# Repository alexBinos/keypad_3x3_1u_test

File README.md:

# keypad_3x3_1u_test

Sharing progress on the 3x3 macro keypad...

## Assembly notes

1. RGB LEDs
   - Pin 1 is marked on the PCB in silkscreen, note that the odd pin on the LED package is GND (pin 3).
   - The LEDs are designed to be placed on the back side of the PCB, facing towards the front, through the cut out.
   - To assist PCB routing, **not all LEDs are oriented in the same direction**, pay close attention to the pin 1 markings on each LED footprint.
   - The cutouts for the bottom most LEDs (D13, D16, D19) was deliberately made 0.4mm wider than the others to test the PCB footprint. This footprint wont be used on future designs.

<br/>

2. Component orientations
   - The pin 1 marker on the KC2016K 16MHz crystal oscillator (X1) and the SRV05-4 TVS diode array (U3) were not placed.
   - With the USB connector facing up:
      - Pin 1 of X1 is the **top right** pad.
      - Pin 1 of U3 is the **top left** pad.

<br/>

3. Entering the bootloader
   - Through the ISP interface, disable the HWBE fuse and enable the BOOTRST fuse.
   - Flash the Caterina bootloader
   - See section 27 of the ATMEGA32U4 datasheet for more details.

<br/>

4. Non-critical hardware bugs
   - The series termination resistor for the RGB LEDs was not placed, the LEDS still work but this may affect their reliability.
   - Pads for the reset switch are slightly too small for the switch provided but you can still make it fit

<br/>

5. If you find any more issues or have feedback for the next revision let me know

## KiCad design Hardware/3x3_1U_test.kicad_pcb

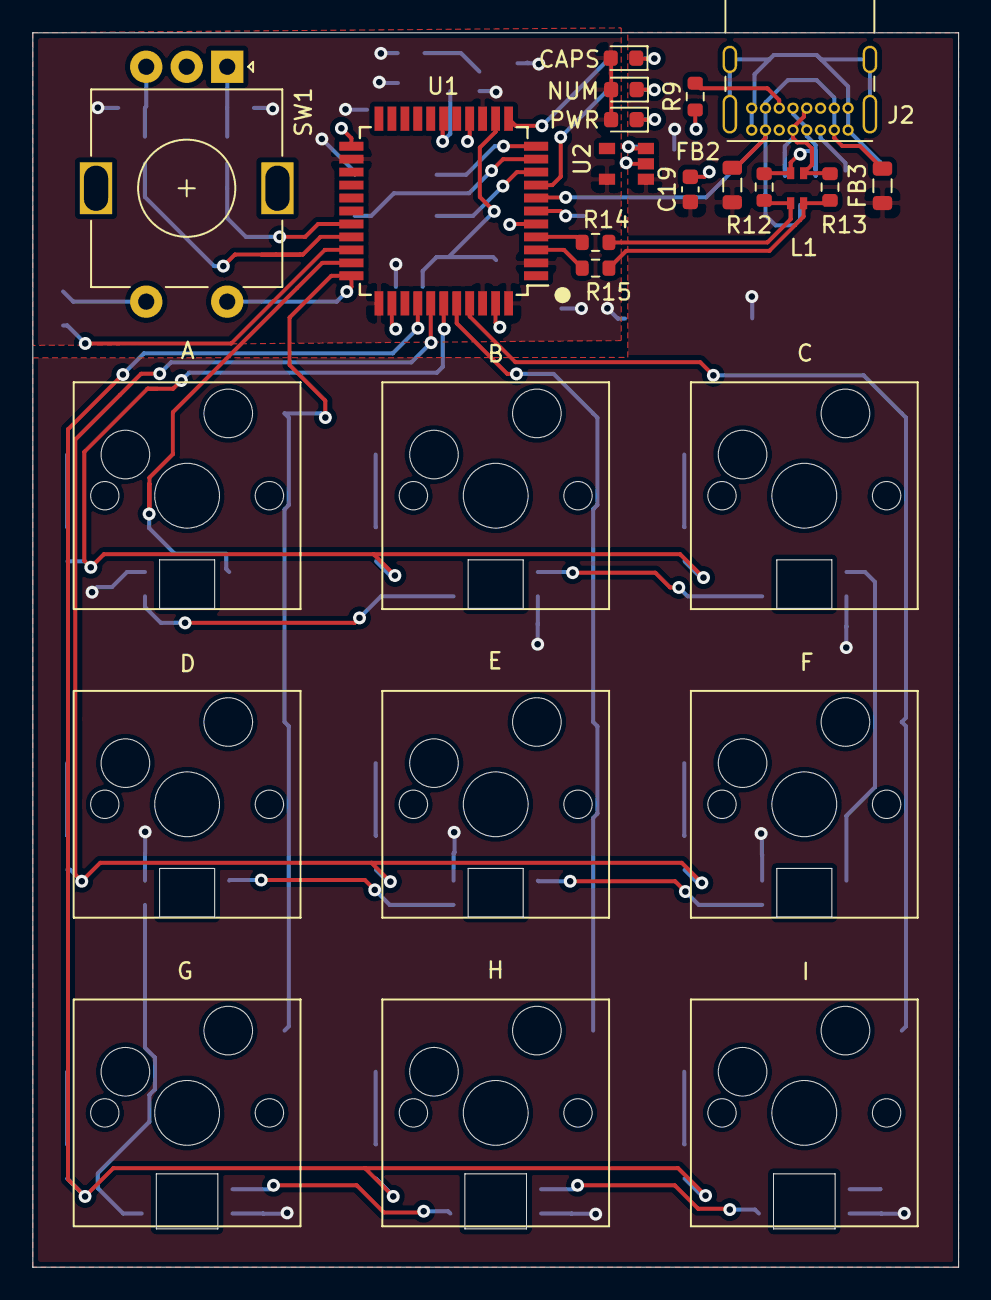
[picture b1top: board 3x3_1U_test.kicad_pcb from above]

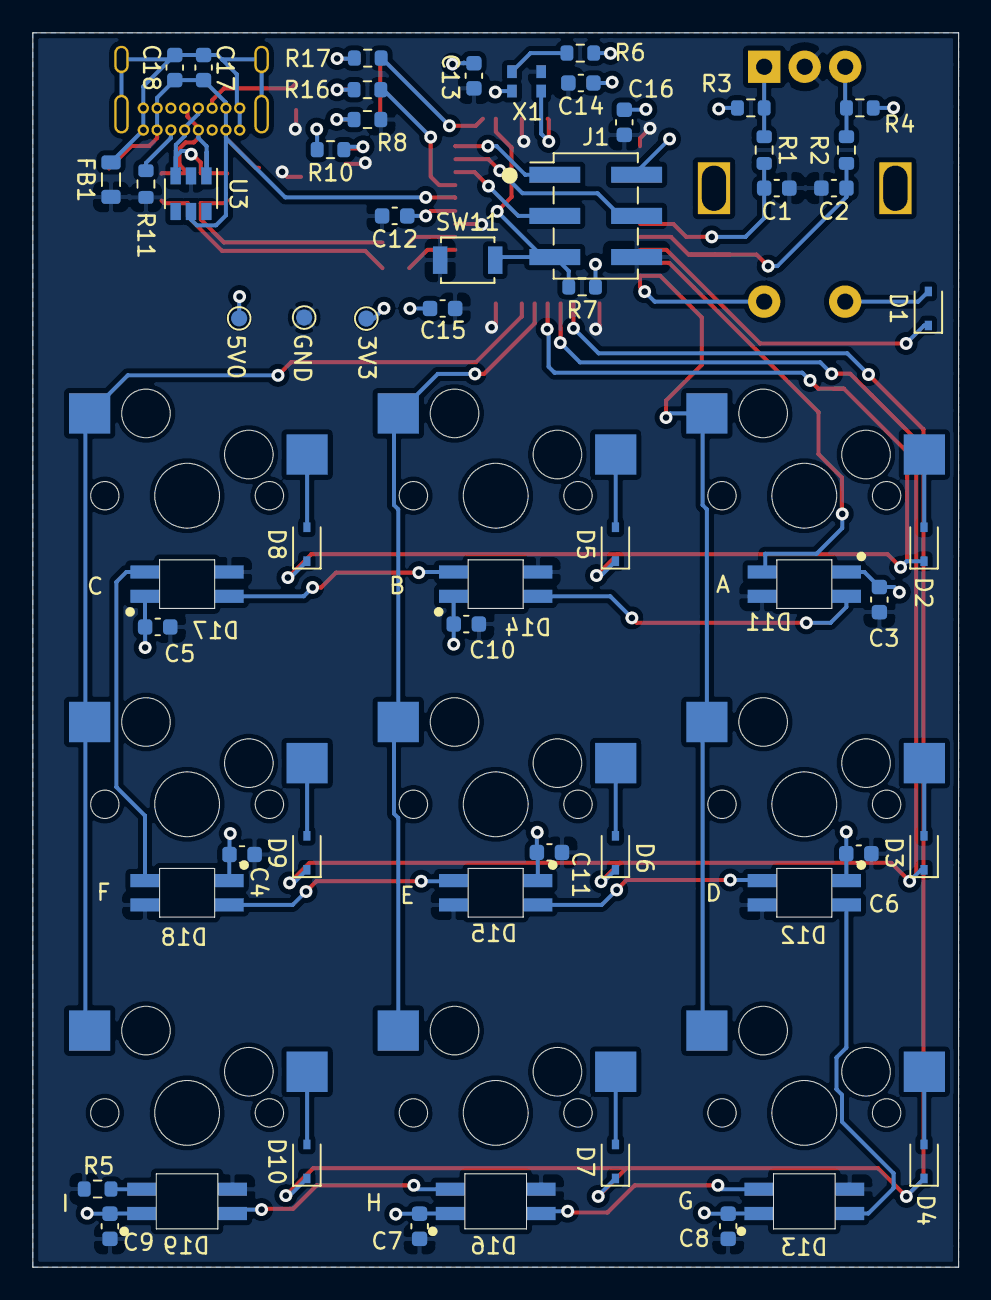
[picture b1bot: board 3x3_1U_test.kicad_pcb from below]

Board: 2 copper layers, 57.2 x 76.2 mm, 82 parts (48 on the bottom side), 57 nets.

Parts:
C1, C2, C3, C4, C5, C6, C7, C8, C9, C10, C11, C13, C14, C15, C19: 100nF; C_0603_1608Metric
C12, C16, C18: 1uF; C_0603_1608Metric
C17: 10uF; C_0603_1608Metric
D1: SWITCH; D_SOD-323
D2: A; D_SOD-323
D3: D; D_SOD-323
D4: G; D_SOD-323
D5: B; D_SOD-323
D6: E; D_SOD-323
D7: H; D_SOD-323
D8: C; D_SOD-323
D9: F; D_SOD-323
D10: I; D_SOD-323
D11: A; SK6812-MINI-E
D12: D; SK6812-MINI-E
D13: G; SK6812-MINI-E_0.4
D14: B; SK6812-MINI-E
D15: E; SK6812-MINI-E
D16: H; SK6812-MINI-E_0.4
D17: C; SK6812-MINI-E
D18: F; SK6812-MINI-E
D19: I; SK6812-MINI-E_0.4
D20, D21, D22: LED; D_0603_1608Metric
FB1, FB2, FB3: Ferrite_Bead; L_0805_2012Metric
J1: Conn_02x03_Odd_Even; PinHeader_2x03_P2.54mm_Vertical_SMD
J2: USB_C_Receptacle_USB2.0; USB_C_Receptacle_GCT_USB4085
L1: L_Core_Iron_Coupled_1423; SMM2012E
R1, R2: 10K; R_0603_1608Metric
R3, R4, R6, R7, R10: 1K; R_0603_1608Metric
R5: Rt; R_0603_1608Metric
R8, R16, R17: 330R; R_0603_1608Metric
R9, R11: 5K1; R_0603_1608Metric
R12, R13: OPT; R_0603_1608Metric
R14, R15: 22R; R_0603_1608Metric
SW1: Rotary_Encoder_Switch; RotaryEncoder_Alps_EC11E-Switch_Vertical_H20mm
SW2: A; CherryMX_1.00u_PCB_KailhSocket
SW3: D; CherryMX_1.00u_PCB_KailhSocket
SW4: G; CherryMX_1.00u_PCB_KailhSocket
SW5: B; CherryMX_1.00u_PCB_KailhSocket
SW6: E; CherryMX_1.00u_PCB_KailhSocket
SW7: H; CherryMX_1.00u_PCB_KailhSocket
SW8: C; CherryMX_1.00u_PCB_KailhSocket
SW9: F; CherryMX_1.00u_PCB_KailhSocket
SW10: I; CherryMX_1.00u_PCB_KailhSocket
SW11: SW_Push; SW_SPST_B3U-1000P
TP1, TP2, TP3: TestPoint; TestPoint_Pad_D1.0mm
U1: ATmega32U4-AU; TQFP-44_10x10mm_P0.8mm
U2: TCR2EF33; TCR2EF33_SOT25
U3: SRV05-4; SOT-23-6
X1: KC2016K

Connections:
+3V3: C13.1, C14.1, C15.1, C16.1, D20.2, D21.2, D22.2, J1.2, R3.1, R4.1, R6.2, R7.1, TP2.1, U1.2, U1.14, U1.24, U1.34, U1.42, U1.44, U2.5, X1.4
+5V: C3.1, C4.1, C5.1, C6.1, C7.1, C8.1, C9.1, C10.1, C11.1, C19.1, D11.1, D12.1, D13.1, D14.1, D15.1, D16.1, D17.1, D18.1, D19.1, FB2.1, FB3.1, R10.2, TP3.1, U2.1
/USB/D+: L1.1, R12.1, R14.2
/USB/D-: L1.2, R13.1, R15.2
COL[0]: SW1.S2, SW2.2, SW3.2, SW4.2, U1.33
COL[1]: SW5.2, SW6.2, SW7.2, U1.40
COL[2]: SW8.2, SW9.2, SW10.2, U1.41
GND: C1.2, C2.2, C3.2, C4.2, C5.2, C6.2, C7.2, C8.2, C9.2, C10.2, C11.2, C12.2, C13.2, C14.2, C15.2, C16.2, C19.2, D11.3, D12.3, D13.3, D14.3, D15.3, D16.3, D17.3, D18.3, D19.3, FB1.1, J1.6, R5.2, R8.1, R9.1, R11.1, SW1.C, SW11.2, TP1.1, U1.5, U1.15, U1.23, U1.35, U1.43, U2.2, U3.2, X1.2
MISO: J1.1, U1.11
MOSI: J1.4, U1.10
unnamed: C12.1, U1.6
unnamed: C17.2, C18.2, FB1.2, J2.A1, J2.A12, J2.B1, J2.B12, J2.S1
unnamed: D1.2, SW1.S1
unnamed: D2.2, SW2.1
unnamed: D3.2, SW3.1
unnamed: D4.2, SW4.1
unnamed: D5.2, SW5.1
unnamed: D6.2, SW6.1
unnamed: D7.2, SW7.1
unnamed: D8.2, SW8.1
unnamed: D9.2, SW9.1
unnamed: D10.2, SW10.1
unnamed: D11.2, D14.4
unnamed: D12.2, D13.4
unnamed: D12.4, D15.2
unnamed: D13.2, D16.4
unnamed: D14.2, D17.4
unnamed: D15.4, D18.2
unnamed: D16.2, D19.4
unnamed: D17.2, D18.4
unnamed: D19.2, R5.1
unnamed: D20.1, R8.2
unnamed: D21.1, R16.2
unnamed: D22.1, R17.2
unnamed: J2.A5, R11.2
unnamed: J2.A6, J2.B6, L1.4, R12.2, U3.3
unnamed: J2.A7, J2.B7, L1.3, R13.2, U3.1
unnamed: J2.B5, R9.2
unnamed: R1.1, R3.2, SW1.A
unnamed: R2.1, R4.2, SW1.B
unnamed: R6.1, X1.1
unnamed: R10.1, U2.3
unnamed: U1.17, X1.3
RGB_OUT: D11.4, U1.32
ROT_ENC_A: C1.1, R1.2, U1.29
ROT_ENC_B: C2.1, R2.2, U1.30
ROW[0]: D2.1, D5.1, D8.1, U1.39
ROW[1]: D3.1, D6.1, D9.1, U1.38
ROW[2]: D4.1, D7.1, D10.1, U1.37
ROW[4]: D1.1, U1.31
RST: J1.5, R7.2, SW11.1, U1.13
SCK: J1.3, U1.9
USBD_N: R15.1, U1.3
USBD_P: R14.1, U1.4
VBUS: C17.1, C18.1, FB2.2, FB3.2, J2.A4, J2.A9, J2.B4, J2.B9, U1.7, U3.5
nCAPS_LOCK: R17.1, U1.12
nNUM_LOCK: R16.1, U1.8

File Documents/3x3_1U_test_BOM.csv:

Id,Designator,Package,Quantity,Designation
1,SW11,SW_SPST_B3U-1000P,1,SW_Push
2,U2,TCR2EF33_SOT25,1,TCR2EF33
3,FB3 FB2 FB1,L_0805_2012Metric,3,Ferrite_Bead
4,D19 D16 D13 D18 D17 D15 D12 D11 D14,SK6812-MINI-E,9,
5,L1,SMM2012E,1,L_Core_Iron_Coupled_1423
6,J2,USB_C_Receptacle_GCT_USB4085,1,USB_C_Receptacle_USB2.0
7,X1,KC2016K,1,KC2016K
8,U3,SOT-23-6,1,SRV05-4
9,U1,TQFP-44_10x10mm_P0.8mm,1,ATmega32U4-AU
10,TP3 TP2 TP1,TestPoint_Pad_D1.0mm,3,TestPoint
11,SW9 SW8 SW7 SW6 SW5 SW4 SW3 SW2 SW1,CherryMX_1.00u_PCB_KailhSocket,9,
12,SW10,RotaryEncoder_Alps_EC11E-Switch_Vertical_H20mm,1,Rotary_Encoder_Switch
13,R17 R16 R8 R5,R_0603_1608Metric,3,330R
14,R15 R14,R_0603_1608Metric,2,22R
15,R13 R12,R_0603_1608Metric,2,OPT
16,R11 R9,R_0603_1608Metric,2,5K1
17,R10 R7 R6 R4 R3,R_0603_1608Metric,5,1K
18,R2 R1,R_0603_1608Metric,2,10K
19,J1,PinHeader_2x03_P2.54mm_Vertical_SMD,1,Conn_02x03_Odd_Even
20,D22 D21 D20,D_0603_1608Metric,3,LED
21,D10 D9 D8 D7 D6 D5 D4 D3 D2 D1,D_SOD-323,10,
22,C19 C15 C14 C13 C11 C10 C9 C8 C7 C6 C5 C4 C3 C2 C1,C_0603_1608Metric,15,100nF
23,C18 C16 C12,C_0603_1608Metric,3,1uF
24,C17,C_0603_1608Metric,1,10uF

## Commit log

2021-07-29 Initial commit- adding design files and datasheets
2021-07-29 Adding BOM file
2021-08-03 Updating readme to include assembly notes
2021-08-12 Adding firmware folder with barebones QMK project
2021-08-12 Updating bootloader section of README
2021-08-13 Adding bin directory with prebuilt .hex file
